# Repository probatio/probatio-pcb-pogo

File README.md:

# probatio-pcb-pogo
PCB for Block's Pogo Pins (Spring Loaded Pins)

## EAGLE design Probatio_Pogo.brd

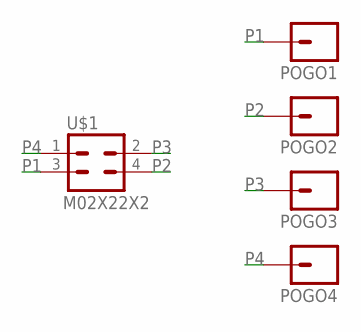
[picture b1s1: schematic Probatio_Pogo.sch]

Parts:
POGO1, POGO2, POGO3, POGO4: POGO_PIN0900-0-15-20-76-14-11-0; POGO_PIN
U$1: M02X22X2; 2X2

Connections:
P1: POGO1.P$1, U$1.3
P2: POGO2.P$1, U$1.4
P3: POGO3.P$1, U$1.2
P4: POGO4.P$1, U$1.1

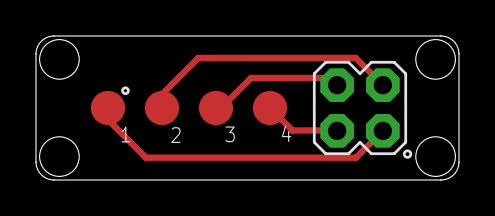
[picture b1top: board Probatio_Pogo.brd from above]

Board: 2 copper layers, 23.5 x 8.0 mm, 5 parts (0 on the bottom side), 4 nets.

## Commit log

2019-08-09 Create LICENSE
2019-08-09 resized width
2019-08-09 Revert "Update Probatio_Pogo.brd"
    This reverts commit b0f66f95d6e1f412cec8757038b3d4162e2bbc9a.
2019-08-09 resized
2019-08-09 allowing gerber files
2019-09-11 Update LICENSE

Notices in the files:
README.md:
License: CC BY-NC-SA 4.0
